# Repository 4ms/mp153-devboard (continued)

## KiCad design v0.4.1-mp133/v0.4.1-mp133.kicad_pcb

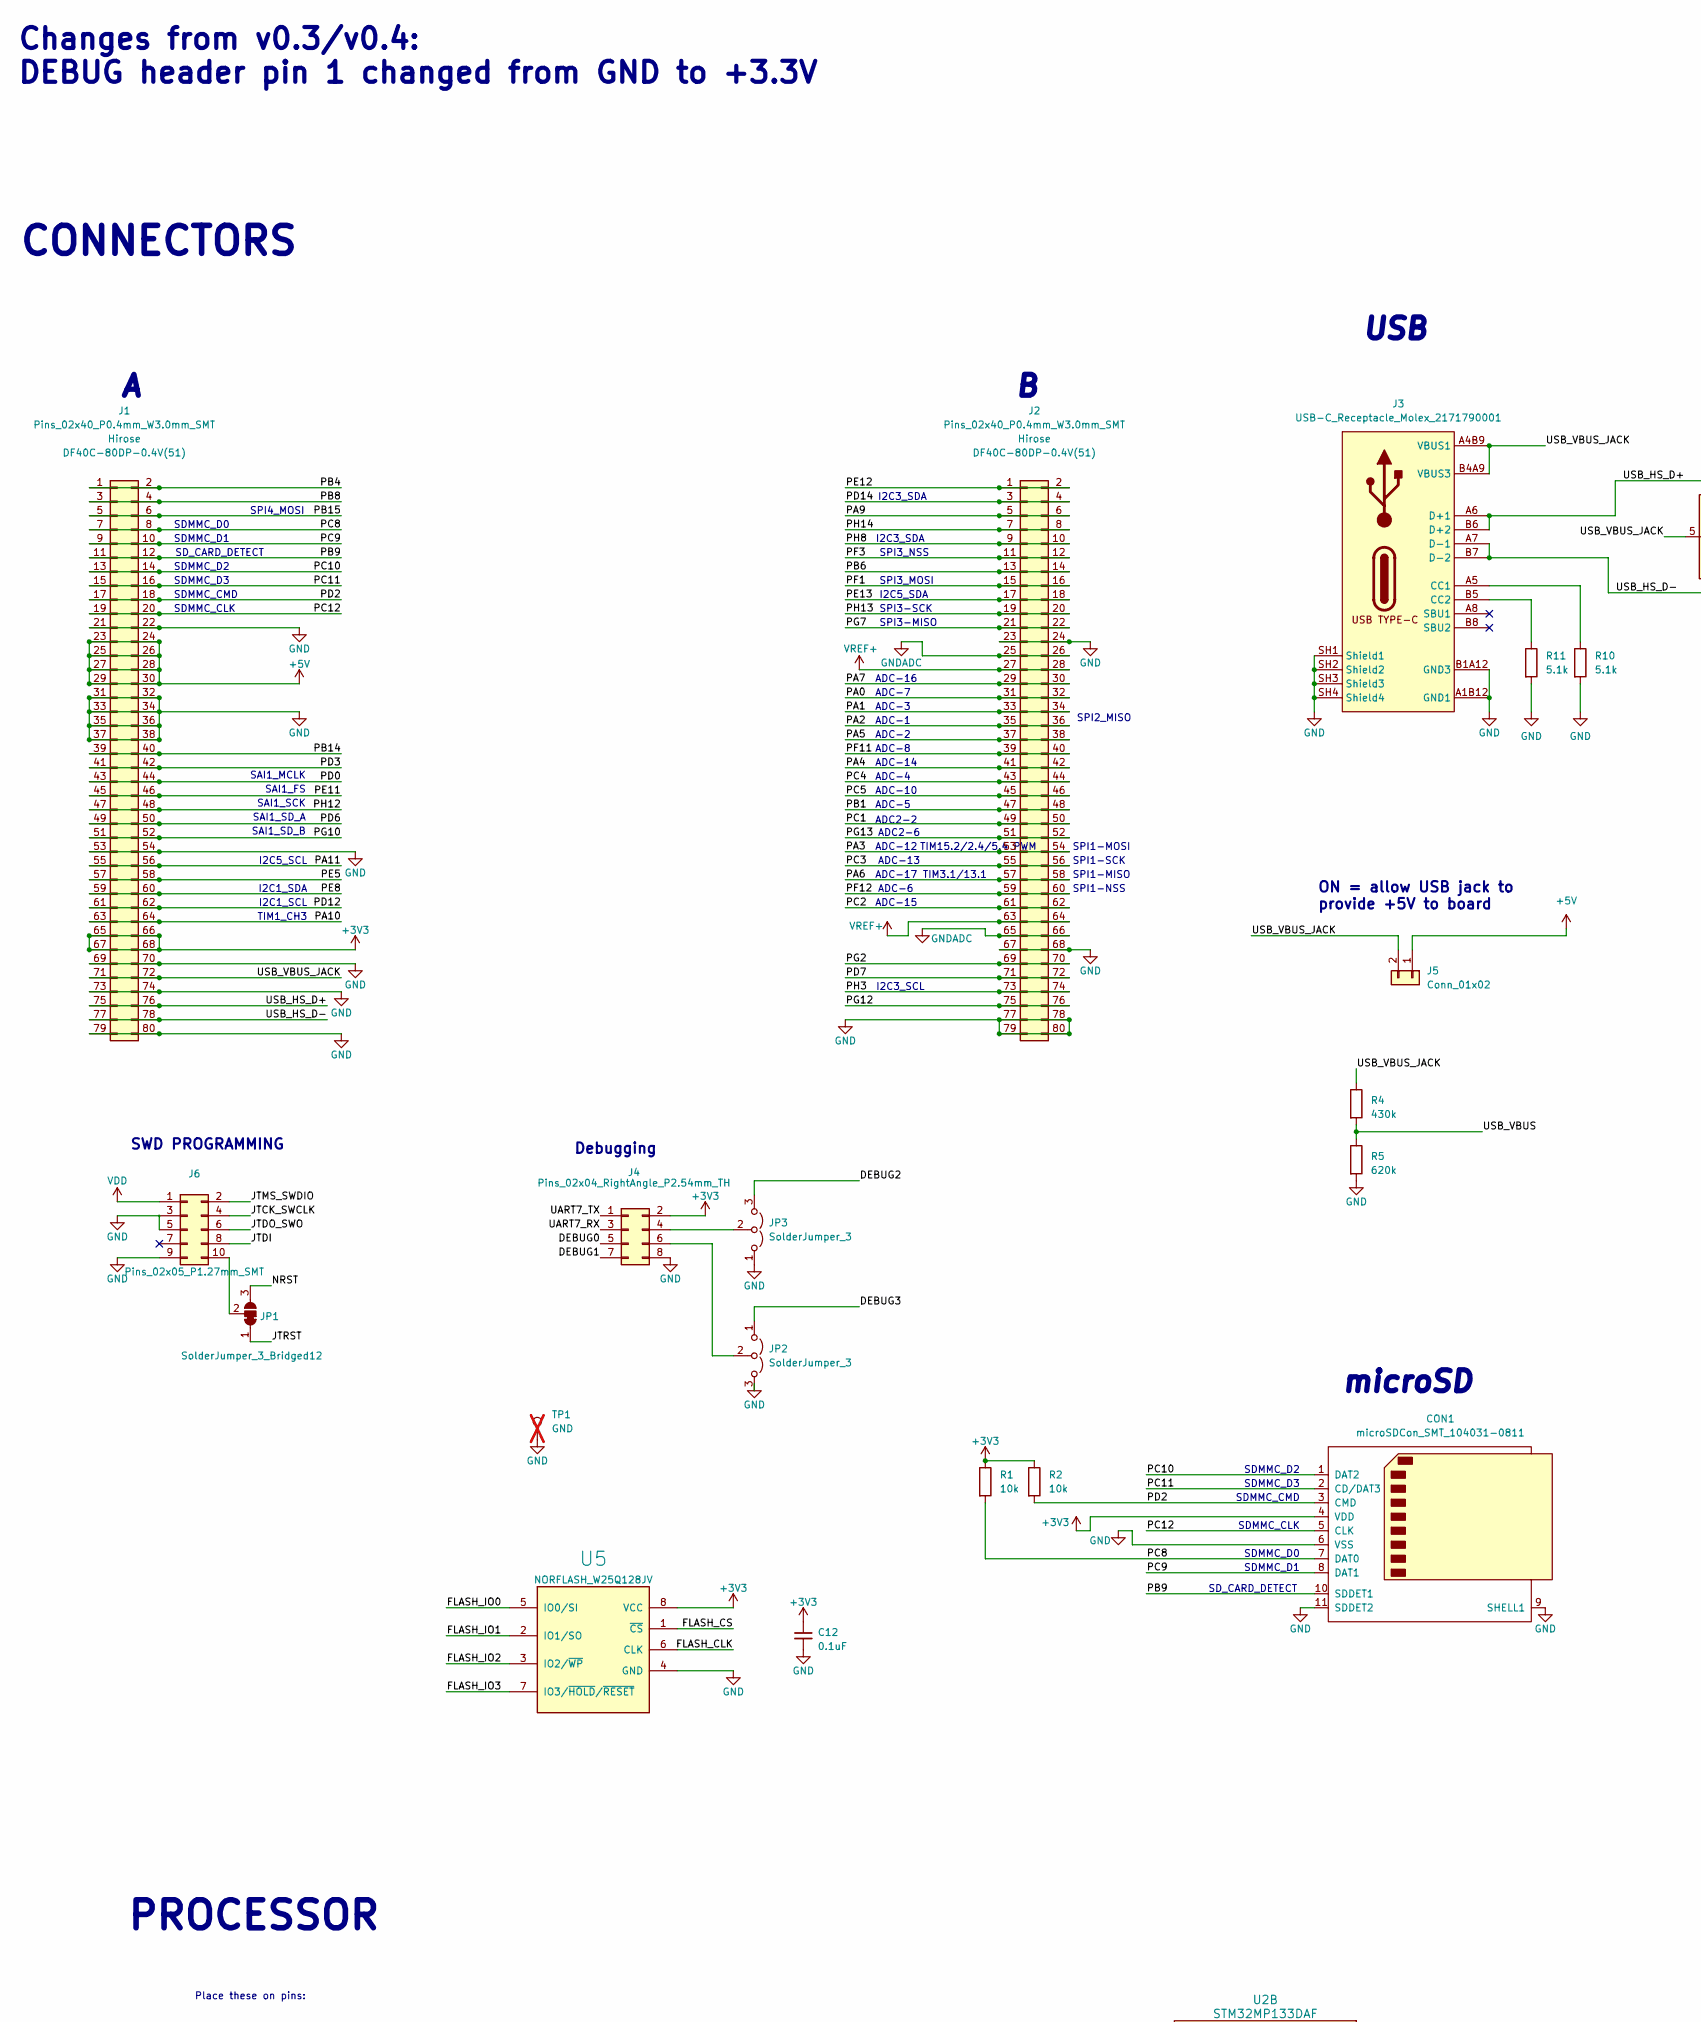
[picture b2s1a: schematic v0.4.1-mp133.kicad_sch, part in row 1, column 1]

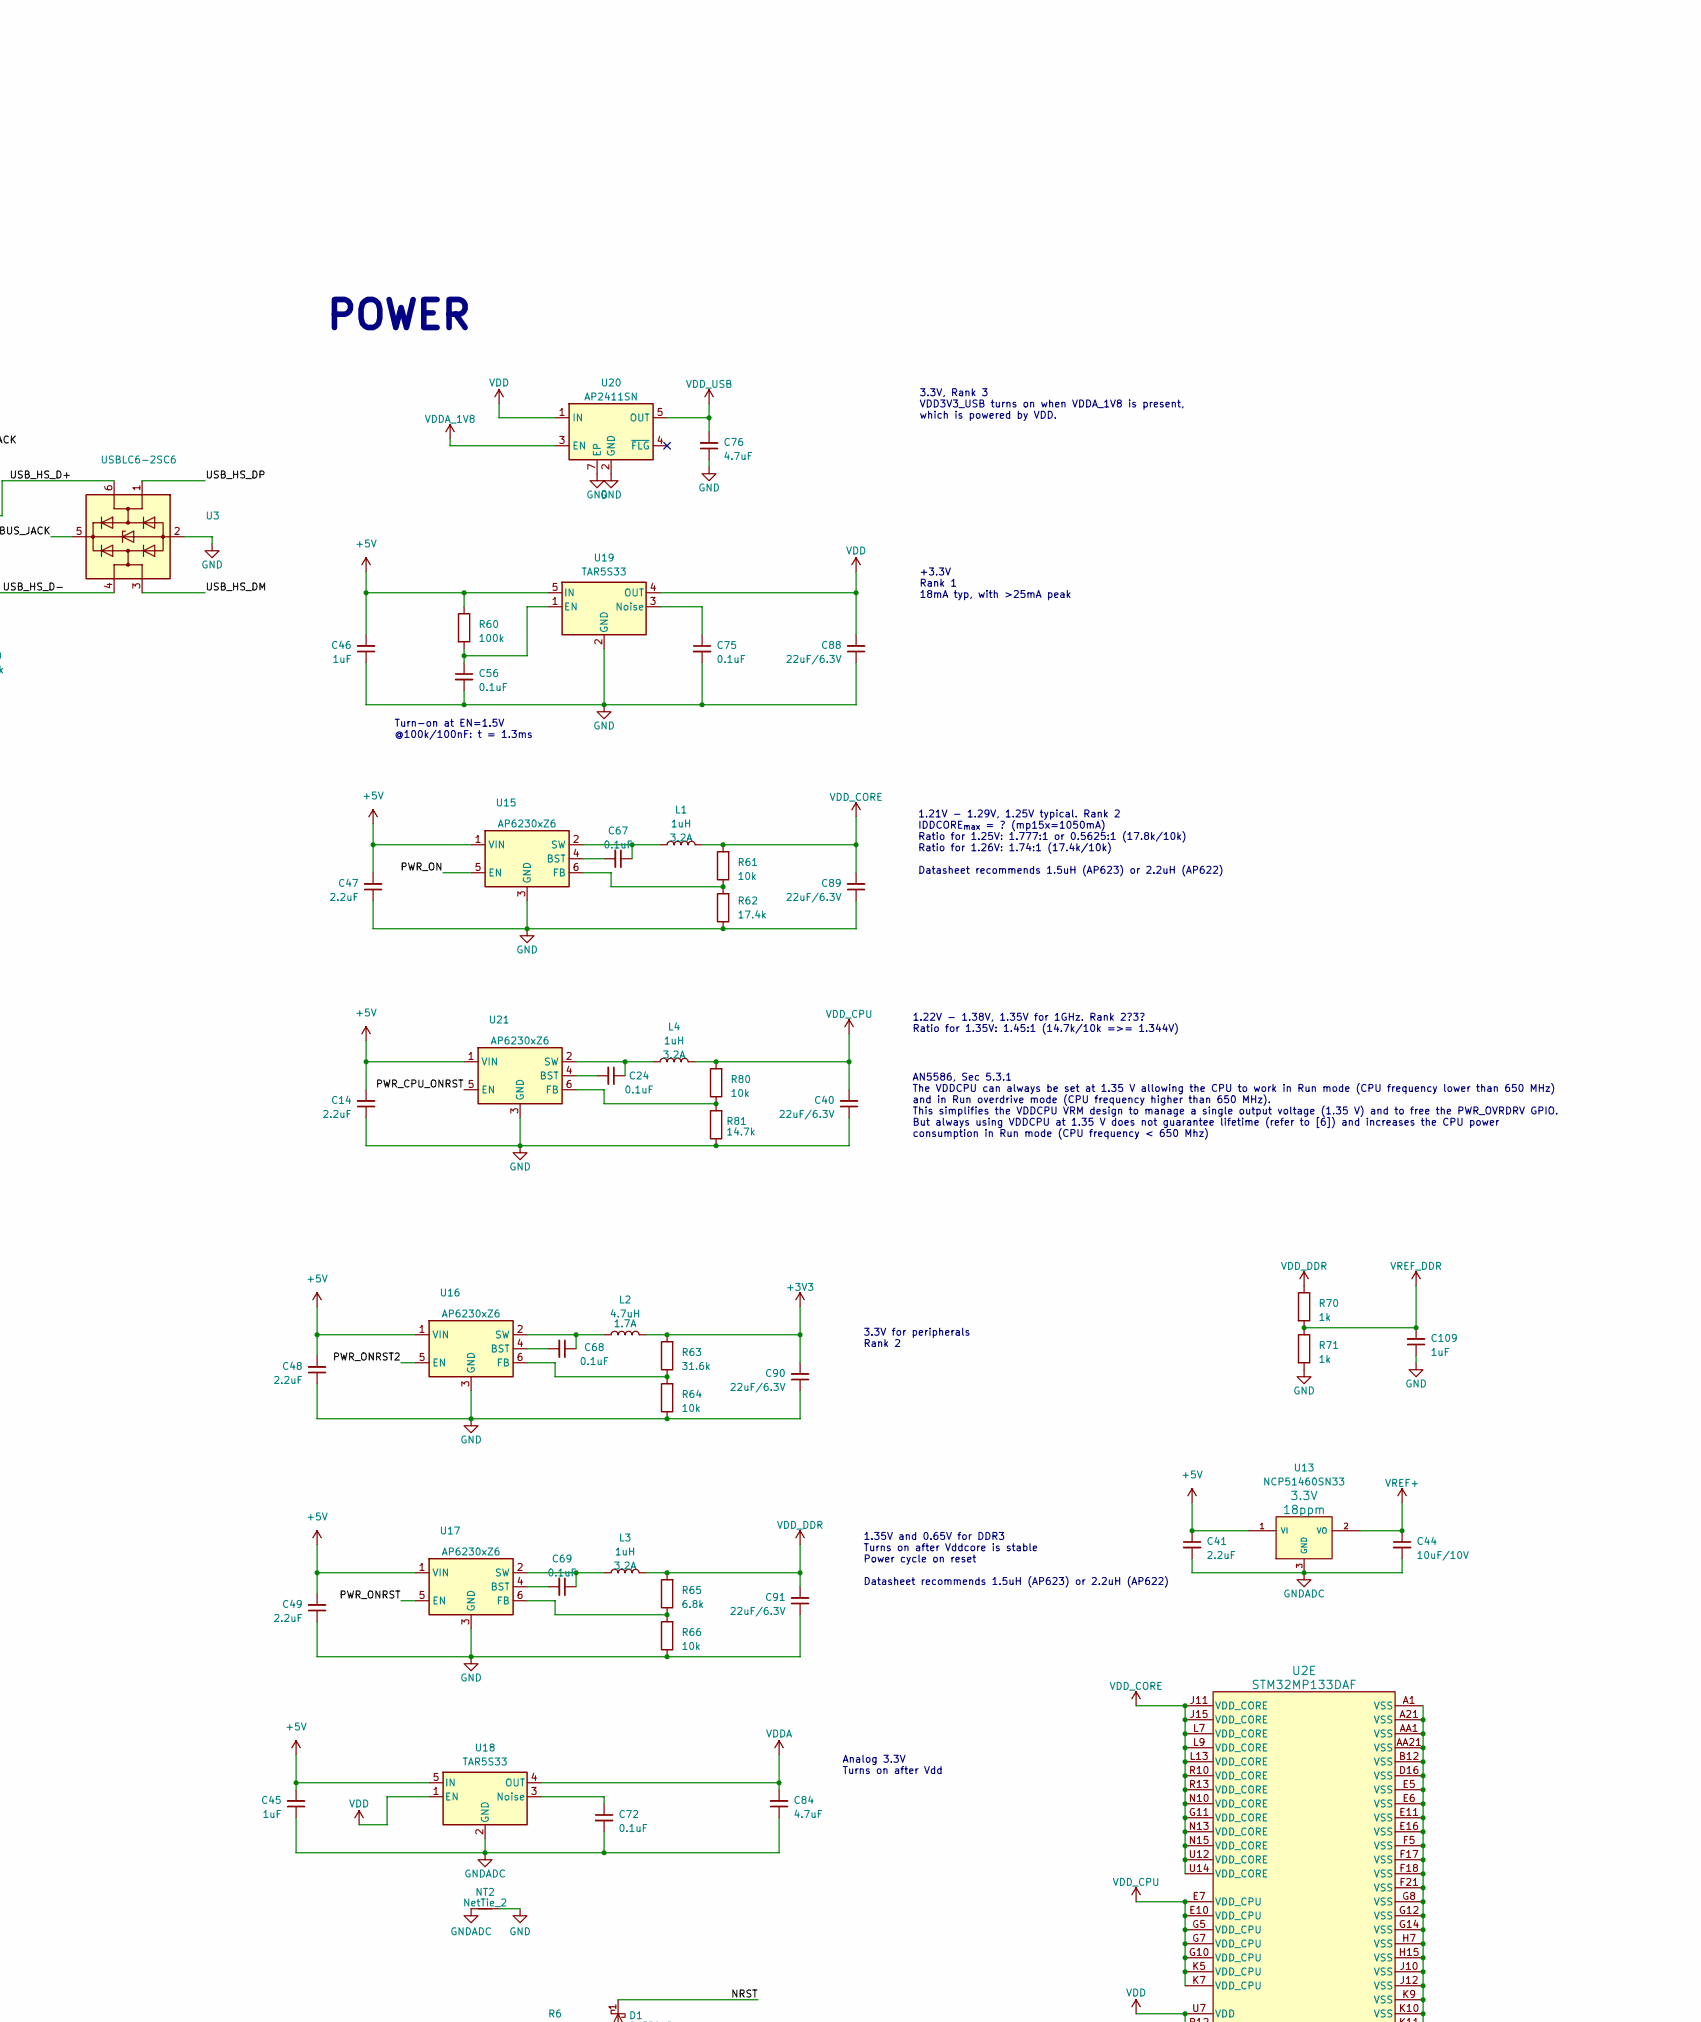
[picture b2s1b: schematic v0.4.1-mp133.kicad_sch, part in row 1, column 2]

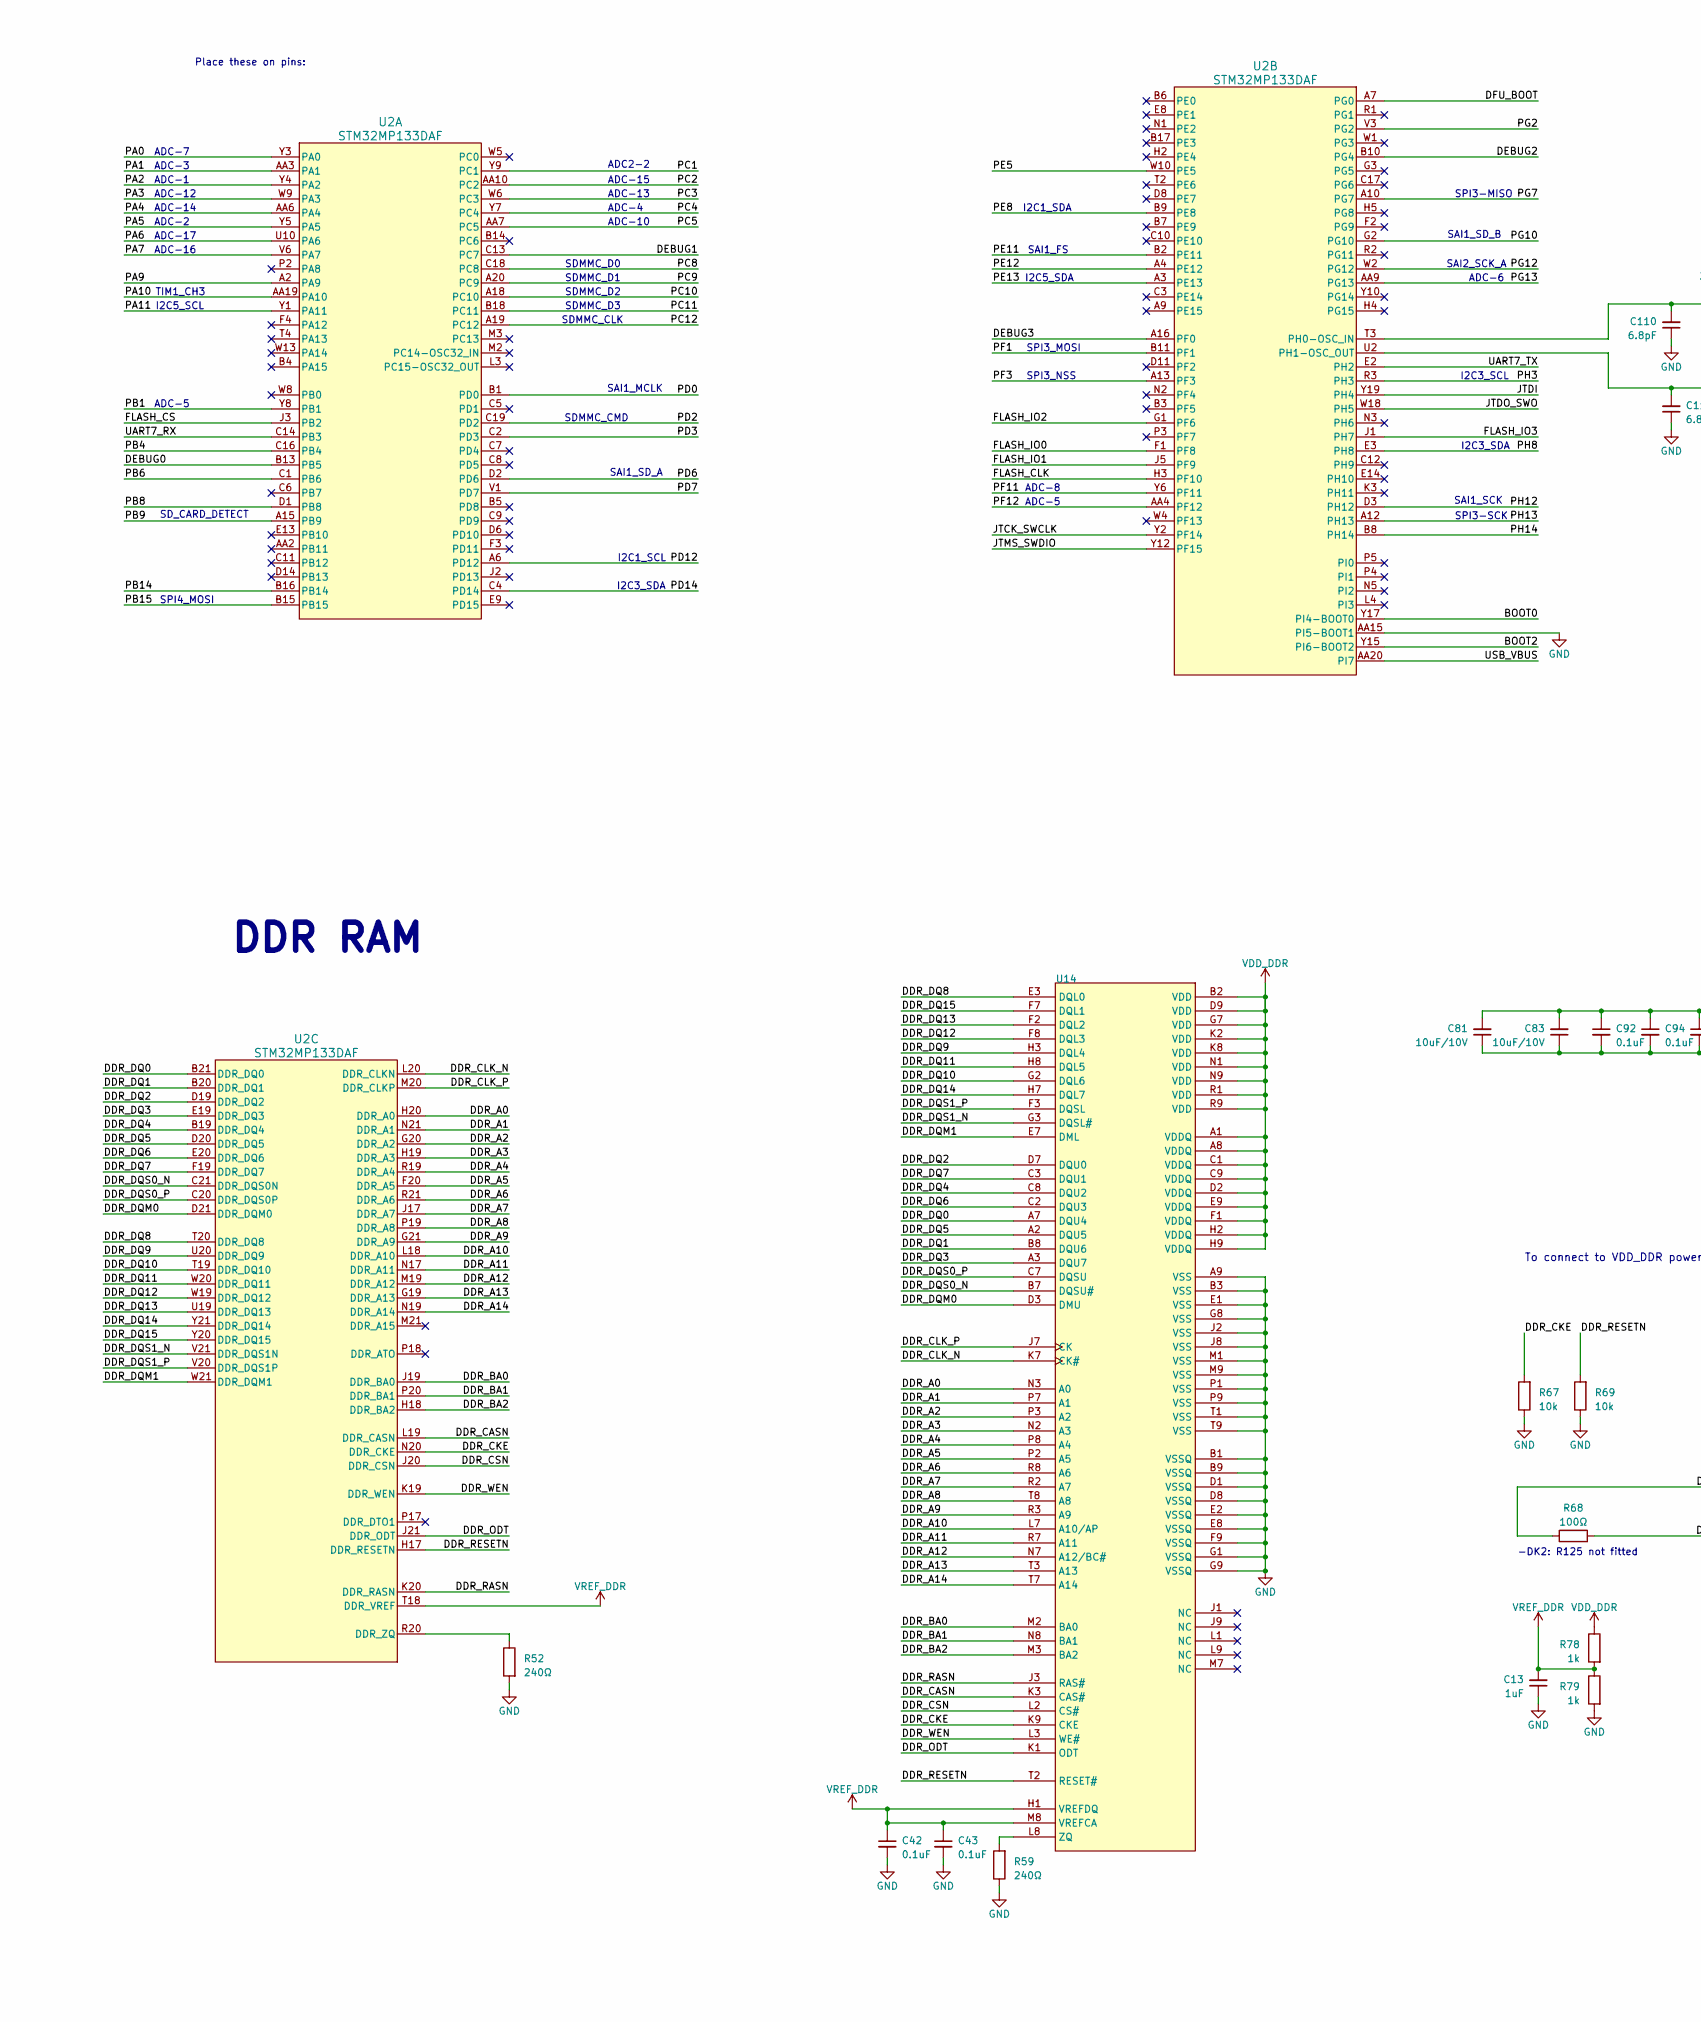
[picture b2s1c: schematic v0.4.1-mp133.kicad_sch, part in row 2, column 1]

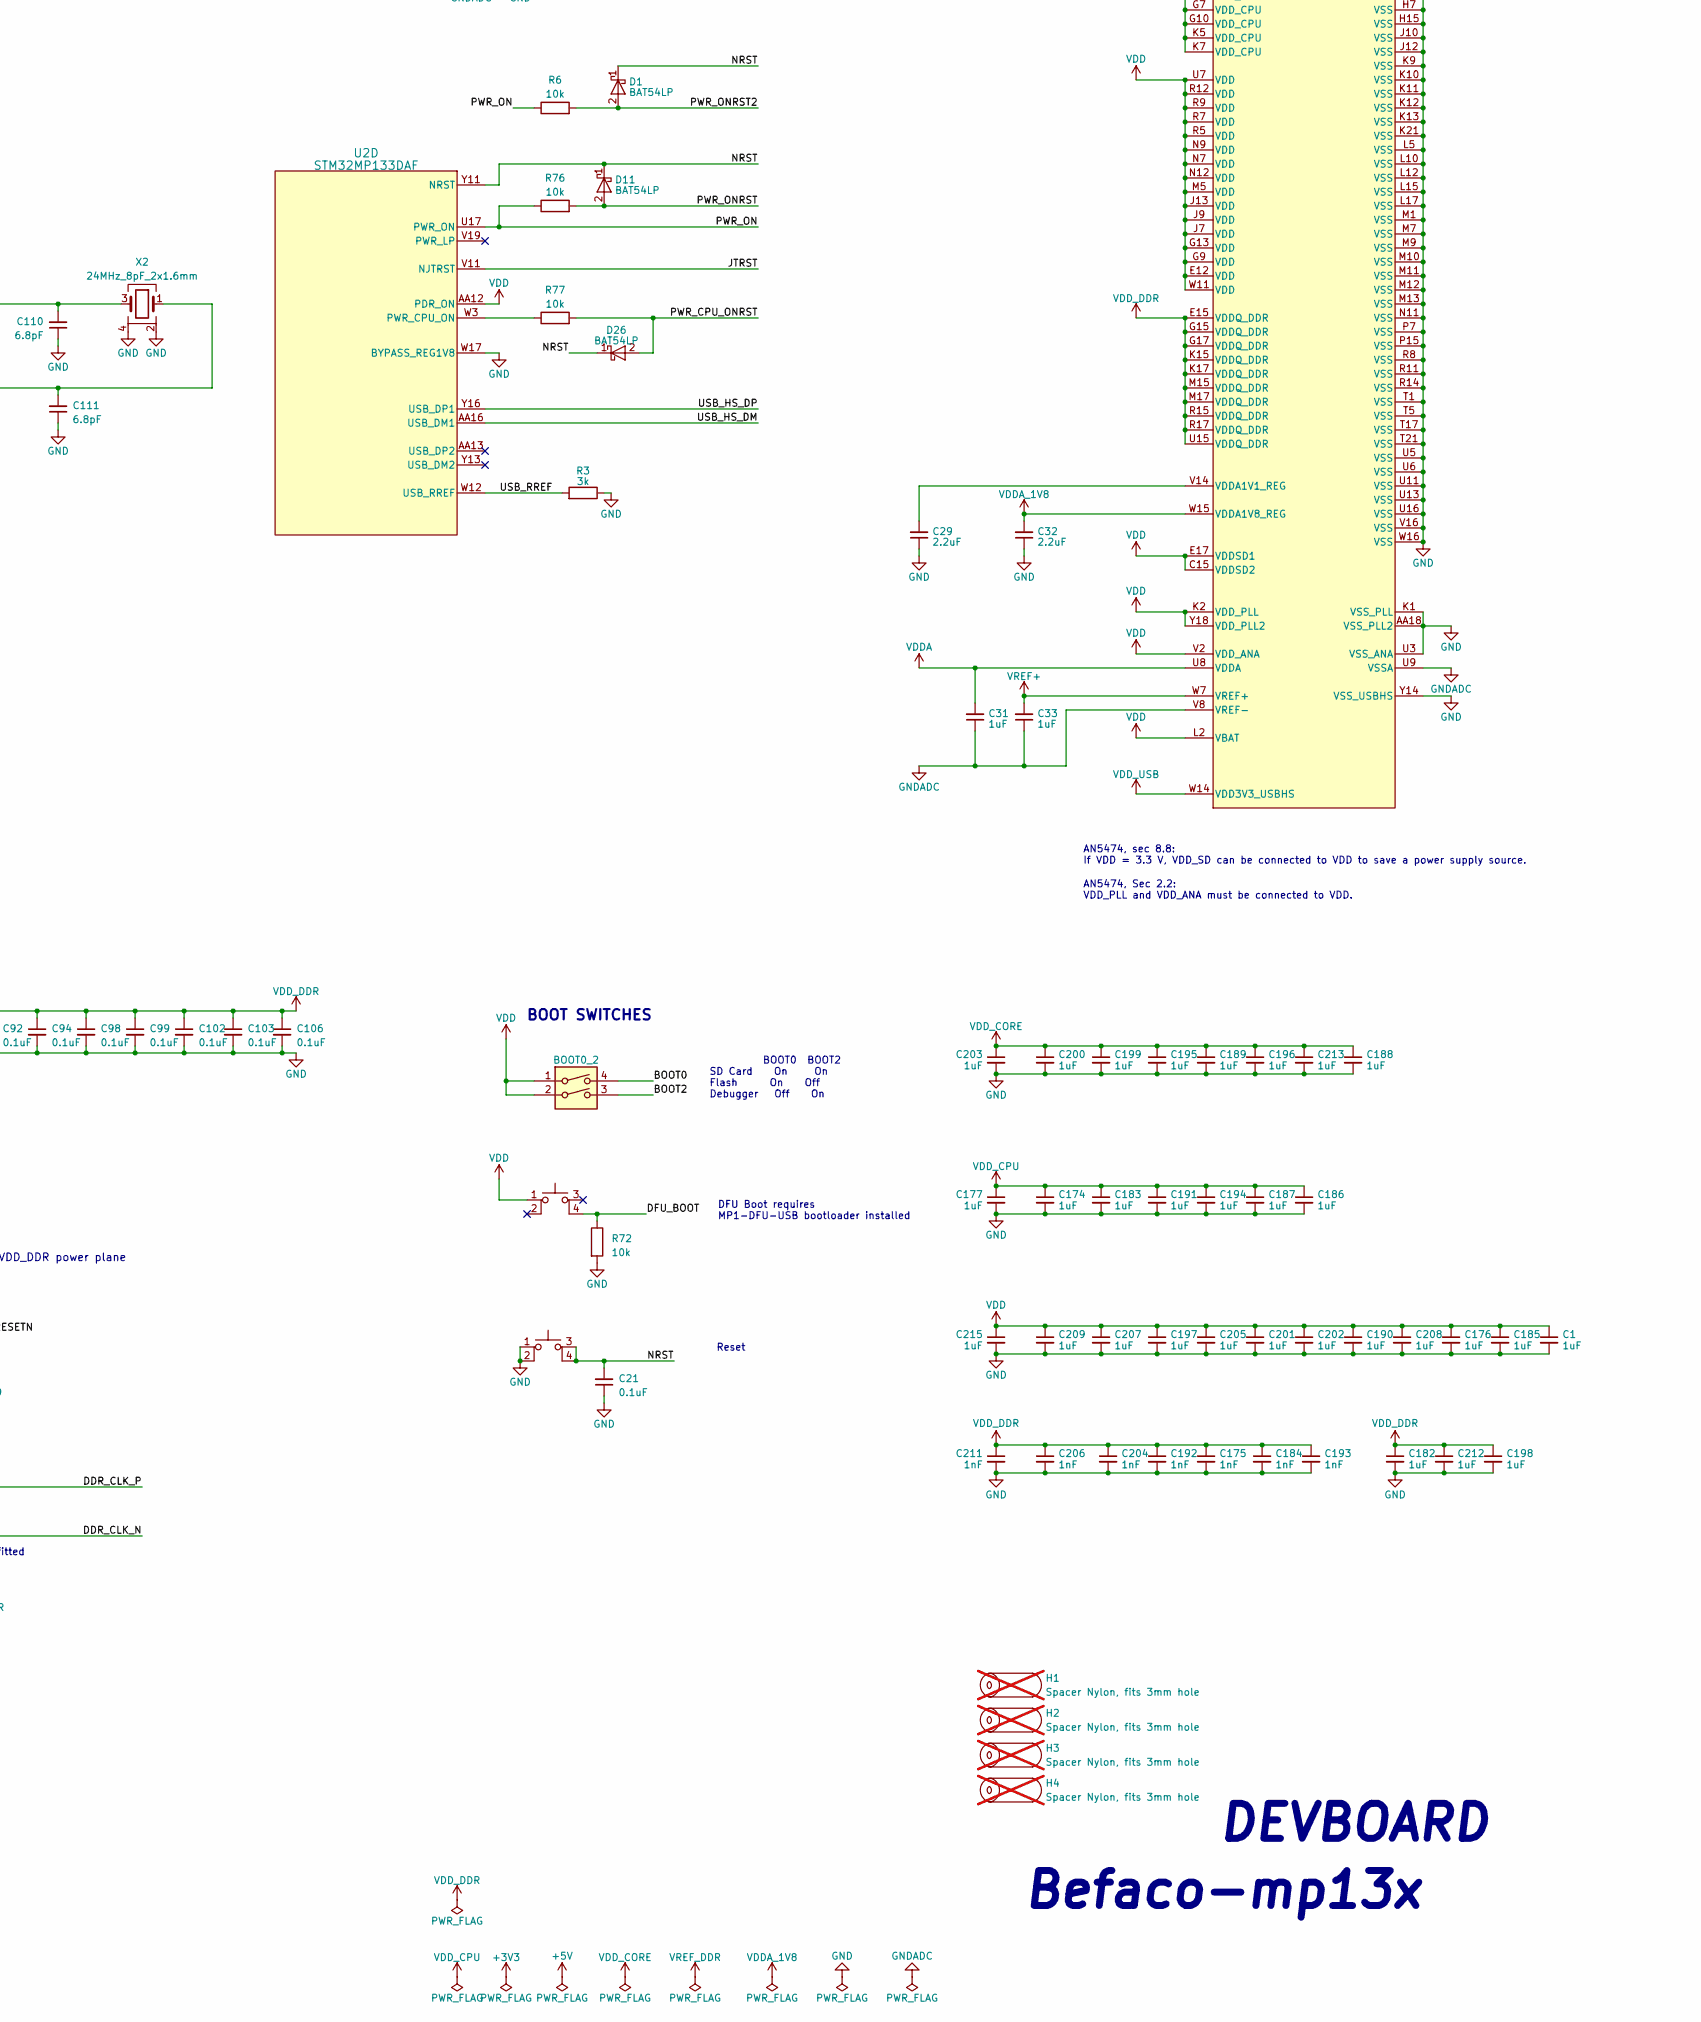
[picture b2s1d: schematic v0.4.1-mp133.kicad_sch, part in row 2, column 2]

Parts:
BOOT0_2: SW_DIP_x02_CTS_219-2MST; SW_DIP_SPSTx02_CTS_219-2MSTR; Part Number 219-2MST; JLCPCB ID C2961978
C1, C174, C176, C177, C182, C183, C185, C186, C187, C188, C189, C190, C191, C194, C195, C196, C197, C198, C199, C200, C201, C202, C203, C205, C207, C208, C209, C212, C213, C215: 1uF_0201_4V; C_0201; Part Number CC0201MRX5R5BB105; JLCPCB ID C272877
C12, C21, C24, C42, C43, C67, C68, C69, C92, C94, C98, C99, C102, C103, C106: 100nF_0402_16V; C_0402; Part Number GCM155R71C104KA55D; JLCPCB ID C1525
C13, C31, C33, C45, C46, C109: 1uF_0402_25V; C_0402; Part Number GMK105CC6105KV-F; JLCPCB ID C52923
C14, C41, C47, C48, C49: 2.2uF_0603_25V; C_0603; Part Number GRM188R6YA225KA12D; JLCPCB ID C57895
C29, C32: 2.2uF_0402_6.3V; C_0402; Part Number GRM155R60J225KE95D; JLCPCB ID C12530
C40, C88, C89, C90, C91: 22uF_0603_6.3V; C_0603; Part Number GRM188R60J226MEA0J; JLCPCB ID C59461
C44, C81, C83: 10uF_0603_10V; C_0603; Part Number GRM188R61A106KE69D; JLCPCB ID C19702
C56, C72, C75: 100nF_0402_50V; C_0402; Part Number GRM155R71H104KE14D; JLCPCB ID C307331
C76, C84: 4.7uF_0402_6.3V; C_0402; Part Number GRM155R60J475ME47; JLCPCB ID C23733
C110, C111: 6.8pF_0402_25V; C_0402; Part Number CC0402CRNPO9BN6R8; JLCPCB ID C1576
C175, C184, C192, C193, C204, C206, C211: 1nF_0201_4V; C_0201; Part Number GRM033R71E102JA01D; JLCPCB ID C258477
CON1: microSDCon_SMT_104031-0811; CardSlot_MicroSD_Molex_104031-0811; Part Number 104031-0811; JLCPCB ID C585350
D1, D11, D26: BAT54LP; DFN-1006-2; Part Number BAT54LP-7; JLCPCB ID C134410
H1, H2, H3, H4: Spacer Nylon, fits 3mm hole; MountingHole_Generic_3mm; not fitted
J1, J2: Pins_02x40_P0.4mm_W3.0mm_SMT; Connector-80pin-P0.4mm-W3.0mm; Part Number DF40C-80DP-0.4V(51); JLCPCB ID C294544
J3: USB-C_Receptacle_Molex_2171790001; USB_C_Receptacle_Molex_2171790001; Part Number 217179-0001; JLCPCB ID C2894899
J4: Pins_02x04_RightAngle_P2.54mm_TH; Pins_2x04_P2.54mm_Horizontal_CroppedSilk; Part Number TSW-104-08-T-D-RA
J5: Conn_01x02; Pins_1x02_2.54mm_TH; Part Number TSW-102-08-T-S-RA
J6: Pins_02x05_P1.27mm_SMT; Pins_2x05_1.27mm_SMD; Part Number FTSH-105-01-F-DV; JLCPCB ID C598540
JP1: SolderJumper_3_Bridged12; JUMPER_SMD_1x3_tiny
JP2, JP3: SolderJumper_3; JUMPER_SMD_1x3_tiny_open
L1, L3, L4: 1uH_3.2A_2520; L_1008_2520Metric; Part Number DFE252012P-1R0M=P2; JLCPCB ID C435392
L2: 4.7uH_1.7A_2510; L_Wuerth_MAPI-2510; Part Number SRN2510F-4R7M; JLCPCB ID C2047781
NT2: NetTie_2; NetTie-2_SMD_Pad0.16mm_6mil
R1, R2, R6, R61, R64, R66, R67, R69, R72, R76, R77, R80: 10k_0402; R_0402; Part Number RC0402FR-0710KL; JLCPCB ID C60490
R3: 3k_0402; R_0402; Part Number RC0402FR-073KL; JLCPCB ID C137987
R4: 430k_0402; R_0402; Part Number RC0402FR-07430KL; JLCPCB ID C163463
R5: 620k_0402; R_0402; Part Number RC0402FR-07620KL; JLCPCB ID C137952
R10, R11: 5.1k_0402; R_0402; Part Number RC0402FR-075K1L; JLCPCB ID C105872
R52, R59: 240Ω_0402; R_0402; Part Number RC0402FR-07240RL; JLCPCB ID C114755
R60: 100k_0402; R_0402; Part Number RC0402FR-07100KL; JLCPCB ID C60491
R62: 17.4k_0402; R_0402; Part Number RC0402FR-0717K4L; JLCPCB ID C327366
R63: 31.6k_0402; R_0402; Part Number RC0402FR-0731K6L; JLCPCB ID C276265
R65: 6.8k_0402; R_0402; Part Number RC0402FR-076K8L; JLCPCB ID C93940
R68: 100Ω_0402; R_0402; Part Number RC0402FR-07100RL; JLCPCB ID C106232
R70, R71, R78, R79: 1k_0402; R_0402; Part Number RC0402FR-071KL; JLCPCB ID C106235
R81: 14.7k_0402; R_0402; Part Number RC0402FR-0714K7L; JLCPCB ID C138055
S2, S3: SW_Push_PTS526 SM15 SMTR2 LFS; Button_Tact_PTS526; Part Number PTS526 SM15 SMTR2 LFS; JLCPCB ID C2689521
TP1: GND; PinHeader_1x01_P2.54mm_Vertical; not fitted
U2: STM32MP133DAF; TFBGA-320_11x11mm_P0.5; Part Number STM32MP133DAF
U3: USBLC6-2SC6; SOT-23-6; Part Number USBLC6-2SC6; JLCPCB ID C2827654
U5: NORFLASH_W25Q128JV; SOIC-8_5.28x4.9mm_Pitch1.27mm; Part Number W25Q128JVSIQ; JLCPCB ID C113767
U13: NCP51460SN33; SOT23-3_PO132; Part Number NCP51460SN33T1G; JLCPCB ID C233715
U14: DDR3L-RAM-4Gb_MT41K256M16TW; FBGA-96_Layout2x3x16_Body8x14_P0.8mm; Part Number MT41K256M16TW-107-P-V00H; JLCPCB ID C253882
U15, U16, U17, U21: AP6230xZ6; SOT-563; Part Number AP62301Z6-7; JLCPCB ID C1880992
U18, U19: TAR5S33; SOT-23-5; Part Number TAR5S33TE85LF; JLCPCB ID C2762700
U20: AP2411SN; DFN-6-1EP_2x2mm_P0.65mm_EP1x1.6mm; Part Number AP2411SN-7; JLCPCB ID C2149815
X2: 24MHz_8pF_2x1.6mm; Crystal_2.0x1.6mm_4pin; Part Number ECS-240-8-37-CKM-TR3; JLCPCB ID C1986107

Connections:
+3V3: C12.1, C90.2, CON1.4 (VDD), J1.65, J1.66, J1.67, J1.68, J4.2, L2.2, R1.1, R2.1, R63.2, U5.8 (VCC)
+5V: C14.2, C41.1, C45.2, C46.2, C47.2, C48.2, C49.2, J1.23, J1.24, J1.25, J1.26, J1.27, J1.28, J1.29, J1.30, J5.1, R60.1, U13.1 (VI), U15.1 (VIN), U16.1 (VIN), U17.1 (VIN), U18.5 (IN), U19.5 (IN), U21.1 (VIN)
/BOOT0: BOOT0_2.4, U2.Y17 (PI4-BOOT0)
/BOOT2: BOOT0_2.3, U2.Y15 (PI6-BOOT2)
/DDR_A0: U2.H20 (DDR_A0), U14.N3 (A0)
/DDR_A1: U2.N21 (DDR_A1), U14.P7 (A1)
/DDR_A2: U2.G20 (DDR_A2), U14.P3 (A2)
/DDR_A3: U2.H19 (DDR_A3), U14.N2 (A3)
/DDR_A4: U2.R19 (DDR_A4), U14.P8 (A4)
/DDR_A5: U2.F20 (DDR_A5), U14.P2 (A5)
/DDR_A6: U2.R21 (DDR_A6), U14.R8 (A6)
/DDR_A7: U2.J17 (DDR_A7), U14.R2 (A7)
/DDR_A8: U2.P19 (DDR_A8), U14.T8 (A8)
/DDR_A9: U2.G21 (DDR_A9), U14.R3 (A9)
/DDR_A10: U2.L18 (DDR_A10), U14.L7 (A10/AP)
/DDR_A11: U2.N17 (DDR_A11), U14.R7 (A11)
/DDR_A12: U2.M19 (DDR_A12), U14.N7 (A12/BC#)
/DDR_A13: U2.G19 (DDR_A13), U14.T3 (A13)
/DDR_A14: U2.N19 (DDR_A14), U14.T7 (A14)
/DDR_BA0: U2.J19 (DDR_BA0), U14.M2 (BA0)
/DDR_BA1: U2.P20 (DDR_BA1), U14.N8 (BA1)
/DDR_BA2: U2.H18 (DDR_BA2), U14.M3 (BA2)
/DDR_CASN: U2.L19 (DDR_CASN), U14.K3 (CAS#)
/DDR_CKE: R67.2, U2.N20 (DDR_CKE), U14.K9 (CKE)
/DDR_CLK_N: R68.2, U2.L20 (DDR_CLKN), U14.K7 (CK#)
/DDR_CLK_P: R68.1, U2.M20 (DDR_CLKP), U14.J7 (CK)
/DDR_CSN: U2.J20 (DDR_CSN), U14.L2 (CS#)
/DDR_DQ0: U2.B21 (DDR_DQ0), U14.A7 (DQU4)
/DDR_DQ1: U2.B20 (DDR_DQ1), U14.B8 (DQU6)
/DDR_DQ2: U2.D19 (DDR_DQ2), U14.D7 (DQU0)
/DDR_DQ3: U2.E19 (DDR_DQ3), U14.A3 (DQU7)
/DDR_DQ4: U2.B19 (DDR_DQ4), U14.C8 (DQU2)
/DDR_DQ5: U2.D20 (DDR_DQ5), U14.A2 (DQU5)
/DDR_DQ6: U2.E20 (DDR_DQ6), U14.C2 (DQU3)
/DDR_DQ7: U2.F19 (DDR_DQ7), U14.C3 (DQU1)
/DDR_DQ8: U2.T20 (DDR_DQ8), U14.E3 (DQL0)
/DDR_DQ9: U2.U20 (DDR_DQ9), U14.H3 (DQL4)
/DDR_DQ10: U2.T19 (DDR_DQ10), U14.G2 (DQL6)
/DDR_DQ11: U2.W20 (DDR_DQ11), U14.H8 (DQL5)
/DDR_DQ12: U2.W19 (DDR_DQ12), U14.F8 (DQL3)
/DDR_DQ13: U2.U19 (DDR_DQ13), U14.F2 (DQL2)
/DDR_DQ14: U2.Y21 (DDR_DQ14), U14.H7 (DQL7)
/DDR_DQ15: U2.Y20 (DDR_DQ15), U14.F7 (DQL1)
/DDR_DQM0: U2.D21 (DDR_DQM0), U14.D3 (DMU)
/DDR_DQM1: U2.W21 (DDR_DQM1), U14.E7 (DML)
/DDR_DQS0_N: U2.C21 (DDR_DQS0N), U14.B7 (DQSU#)
/DDR_DQS0_P: U2.C20 (DDR_DQS0P), U14.C7 (DQSU)
/DDR_DQS1_N: U2.V21 (DDR_DQS1N), U14.G3 (DQSL#)
/DDR_DQS1_P: U2.V20 (DDR_DQS1P), U14.F3 (DQSL)
/DDR_ODT: U2.J21 (DDR_ODT), U14.K1 (ODT)
/DDR_RASN: U2.K20 (DDR_RASN), U14.J3 (RAS#)
/DDR_RESETN: R69.2, U2.H17 (DDR_RESETN), U14.T2 (RESET#)
/DDR_WEN: U2.K19 (DDR_WEN), U14.L3 (WE#)
/DEBUG0: J4.5, U2.B13 (PB5)
/DEBUG1: J4.7, U2.C13 (PC7)
/DEBUG2: JP3.3 (B), U2.B10 (PG4)
/DEBUG3: JP2.1 (A), U2.A16 (PF0)
/DFU_BOOT: R72.1, S3.4, U2.A7 (PG0)
/FLASH_CLK: U2.H3 (PF10), U5.6 (CLK)
/FLASH_CS: U2.J3 (PB2), U5.1 (~CS)
/FLASH_IO0: U2.F1 (PF8), U5.5 (IO0/SI)
/FLASH_IO1: U2.J5 (PF9), U5.2 (IO1/SO)
/FLASH_IO2: U2.G1 (PF6), U5.3 (IO2/~WP)
/FLASH_IO3: U2.J1 (PH7), U5.7 (IO3/~HOLD/~RESET)
/JTCK_SWCLK: J6.4, U2.Y2 (PF14)
/JTDI: J6.8, U2.Y19 (PH4)
/JTDO_SWO: J6.6, U2.W18 (PH5)
/JTMS_SWDIO: J6.2, U2.Y12 (PF15)
/JTRST: JP1.1 (A), U2.V11 (NJTRST)
/NRST: C21.2, D1.1 (K), D11.1 (K), D26.1 (K), JP1.3 (B), S2.3, S2.4, U2.Y11 (NRST)
/PA0: J2.31, J2.32, U2.Y3 (PA0)
/PA1: J2.33, J2.34, U2.AA3 (PA1)
/PA2: J2.35, J2.36, U2.Y4 (PA2)
/PA3: J2.53, J2.54, U2.W9 (PA3)
/PA4: J2.41, J2.42, U2.AA6 (PA4)
/PA5: J2.37, J2.38, U2.Y5 (PA5)
/PA6: J2.57, J2.58, U2.U10 (PA6)
/PA7: J2.29, J2.30, U2.V6 (PA7)
/PA9: J2.5, J2.6, U2.A2 (PA9)
/PA10: J1.63, J1.64, U2.AA19 (PA10)
/PA11: J1.55, J1.56, U2.Y1 (PA11)
/PB1: J2.47, J2.48, U2.Y8 (PB1)
/PB4: J1.1, J1.2, U2.C16 (PB4)
/PB6: J2.13, J2.14, U2.C1 (PB6)
/PB8: J1.3, J1.4, U2.D1 (PB8)
/PB9: CON1.10 (SDDET1), J1.11, J1.12, U2.A15 (PB9)
/PB14: J1.39, J1.40, U2.B16 (PB14)
/PB15: J1.5, J1.6, U2.B15
/PC1: J2.49, J2.50, U2.Y9 (PC1)
/PC2: J2.61, J2.62, U2.AA10 (PC2)
/PC3: J2.55, J2.56, U2.W6 (PC3)
/PC4: J2.43, J2.44, U2.Y7 (PC4)
/PC5: J2.45, J2.46, U2.AA7 (PC5)
/PC8: CON1.7 (DAT0), J1.7, J1.8, R1.2, U2.C18 (PC8)
/PC9: CON1.8 (DAT1), J1.9, J1.10, U2.A20 (PC9)
/PC10: CON1.1 (DAT2), J1.13, J1.14, U2.A18 (PC10)
/PC11: CON1.2 (CD/DAT3), J1.15, J1.16, U2.B18 (PC11)
/PC12: CON1.5 (CLK), J1.19, J1.20, U2.A19 (PC12)
/PD0: J1.43, J1.44, U2.B1 (PD0)
/PD2: CON1.3 (CMD), J1.17, J1.18, R2.2, U2.C19 (PD2)
/PD3: J1.41, J1.42, U2.C2 (PD3)
/PD6: J1.49, J1.50, U2.D2 (PD6)
/PD7: J2.71, J2.72, U2.V1 (PD7)
/PD12: J1.61, J1.62, U2.A6 (PD12)
/PD14: J2.3, J2.4, U2.C4 (PD14)
/PE5: J1.57, J1.58, U2.W10 (PE5)
/PE8: J1.59, J1.60, U2.B9 (PE8)
/PE11: J1.45, J1.46, U2.B2 (PE11)
/PE12: J2.1, J2.2, U2.A4 (PE12)
/PE13: J2.17, J2.18, U2.A3 (PE13)
/PF1: J2.15, J2.16, U2.B11 (PF1)
/PF3: J2.11, J2.12, U2.A13 (PF3)
/PF11: J2.39, J2.40, U2.Y6 (PF11)
/PF12: J2.59, J2.60, U2.AA4 (PF12)
/PG2: J2.69, J2.70, U2.V3 (PG2)
/PG7: J2.21, J2.22, U2.A10 (PG7)
/PG10: J1.51, J1.52, U2.G2 (PG10)
/PG12: J2.75, J2.76, U2.W2 (PG12)
/PG13: J2.51, J2.52, U2.AA9 (PG13)
/PH3: J2.73, J2.74, U2.R3 (PH3)
/PH8: J2.9, J2.10, U2.E3 (PH8)
/PH12: J1.47, J1.48, U2.D3 (PH12)
/PH13: J2.19, J2.20, U2.A12 (PH13)
/PH14: J2.7, J2.8, U2.B8 (PH14)
/PWR_CPU_ONRST: D26.2 (A), R77.2, U21.5 (EN)
/PWR_ON: R6.1, R76.1, U2.U17 (PWR_ON), U15.5 (EN)
/PWR_ONRST: D11.2 (A), R76.2, U17.5 (EN)
/PWR_ONRST2: D1.2 (A), R6.2, U16.5 (EN)
/UART7_RX: J4.3, U2.C14 (PB3)
/UART7_TX: J4.1, U2.E2 (PH2)
/USB_HS_D+: J1.75, J1.76, J3.A6 (D+1), J3.B6 (D+2), U3.6 (I/O1)
/USB_HS_D-: J1.77, J1.78, J3.A7 (D-1), J3.B7 (D-2), U3.4 (I/O2)
/USB_HS_DM: U2.AA16 (USB_DM1), U3.3 (I/O2)
/USB_HS_DP: U2.Y16 (USB_DP1), U3.1 (I/O1)
/USB_RREF: R3.2, U2.W12 (USB_RREF)
/USB_VBUS: R4.2, R5.1, U2.AA20 (PI7)
/USB_VBUS_JACK: J1.71, J1.72, J3.A4B9 (VBUS1), J3.B4A9 (VBUS3), J5.2, R4.1, U3.5 (VBUS)
GND: C1.2, C12.2, C13.1, C14.1, C21.1, C29.1, C32.1, C40.1, C42.2, C43.2, C46.1, C47.1, C48.1, C49.1, C56.2, C75.2, C76.1, C81.1, C83.1, C88.1, C89.1, C90.1, C91.1, C92.2, C94.2, C98.2, C99.2, C102.2, C103.2, C106.2, C109.1, C110.1, C111.1, C174.2, C175.2, C176.2, C177.2, C182.2, C183.2, C184.2, C185.2, C186.2, C187.2, C188.2, C189.2, C190.2, C191.2, C192.2, C193.2, C194.2, C195.2, C196.2, C197.2, C198.2, C199.2, C200.2, C201.2, C202.2, C203.2, C204.2, C205.2, C206.2, C207.2, C208.2, C209.2, C211.2, C212.2, C213.2, C215.2, CON1.6 (VSS), CON1.9 (SHELL1), CON1.11 (SDDET2), J1.21, J1.22, J1.31, J1.32, J1.33, J1.34, J1.35, J1.36, J1.37, J1.38, J1.53, J1.54, J1.69, J1.70, J1.73, J1.74, J1.79, J1.80, J2.23, J2.24, J2.67, J2.68, J2.77, J2.78, J2.79, J2.80, J3.A1B12 (GND1), J3.B1A12 (GND3), J3.SH1 (Shield1), J3.SH2 (Shield2), J3.SH3 (Shield3), J3.SH4 (Shield4), J4.8, J6.3, J6.5, J6.9, JP2.3 (B), JP3.1 (A), NT2.2, R3.1, R5.2, R10.2, R11.2, R52.2, R59.1, R62.1, R64.1, R66.1, R67.1, R69.1, R71.2, R72.2, R79.2, R81.1, S2.1, S2.2, TP1.1, U2.A1 (VSS), U2.A21 (VSS), U2.AA1 (VSS), U2.AA15 (PI5-BOOT1), U2.AA18 (VSS_PLL2), U2.AA21 (VSS), U2.B12 (VSS), U2.D16 (VSS), U2.E5 (VSS), U2.E6 (VSS), U2.E11 (VSS), U2.E16 (VSS), U2.F5 (VSS), U2.F17 (VSS), U2.F18 (VSS), U2.F21 (VSS), U2.G8 (VSS), U2.G12 (VSS), U2.G14 (VSS), U2.H7 (VSS), U2.H15 (VSS), U2.J10 (VSS), U2.J12 (VSS), U2.K1 (VSS_PLL), U2.K9 (VSS), U2.K10 (VSS), U2.K11 (VSS), U2.K12 (VSS), U2.K13 (VSS), U2.K21 (VSS), U2.L5 (VSS), U2.L10 (VSS), U2.L12 (VSS), U2.L15 (VSS), U2.L17 (VSS), U2.M1 (VSS), U2.M7 (VSS), U2.M9 (VSS), U2.M10 (VSS), U2.M11 (VSS), U2.M12 (VSS), U2.M13 (VSS), U2.N11 (VSS), U2.P7 (VSS), U2.P15 (VSS), U2.R8 (VSS), U2.R11 (VSS), U2.R14 (VSS), U2.T1 (VSS), U2.T5 (VSS), U2.T17 (VSS), U2.T21 (VSS), U2.U3 (VSS_ANA), U2.U5 (VSS), U2.U6 (VSS), U2.U11 (VSS), U2.U13 (VSS), U2.U16 (VSS), U2.V16 (VSS), U2.W16 (VSS), U2.W17 (BYPASS_REG1V8), U2.Y14 (VSS_USBHS), U3.2 (GND), U5.4 (GND), U14.A9 (VSS), U14.B1 (VSSQ), U14.B3 (VSS), U14.B9 (VSSQ), U14.D1 (VSSQ), U14.D8 (VSSQ), U14.E1 (VSS), U14.E2 (VSSQ), U14.E8 (VSSQ), U14.F9 (VSSQ), U14.G1 (VSSQ), U14.G8 (VSS), U14.G9 (VSSQ), U14.J2 (VSS), U14.J8 (VSS), U14.M1 (VSS), U14.M9 (VSS), U14.P1 (VSS), U14.P9 (VSS), U14.T1 (VSS), U14.T9 (VSS), U15.3 (GND), U16.3 (GND), U17.3 (GND), U19.2 (GND), U20.2 (GND), U20.7 (EP), U21.3 (GND), X2.2, X2.4
GNDADC: C31.1, C33.1, C41.2, C44.2, C45.1, C72.2, C84.1, J2.25, J2.26, J2.65, J2.66, NT2.1, U2.U9 (VSSA), U2.V8 (VREF-), U13.3 (GND), U18.2 (GND)
unnamed: J3.A5 (CC1), R10.1
unnamed: J3.B5 (CC2), R11.1
unnamed: J4.4, JP3.2 (C)
unnamed: J4.6, JP2.2 (C)
unnamed: J6.10, JP1.2 (C)
unnamed: C110.2, U2.T3 (PH0-OSC_IN), X2.3
unnamed: C111.2, U2.U2 (PH1-OSC_OUT), X2.1
unnamed: R52.1, U2.R20 (DDR_ZQ)
unnamed: R77.1, U2.W3 (PWR_CPU_ON)
unnamed: C29.2, U2.V14 (VDDA1V1_REG)
unnamed: R59.2, U14.L8 (ZQ)
unnamed: C67.2, U15.4 (BST)
unnamed: R61.1, R62.2, U15.6 (FB)
unnamed: C67.1, L1.1, U15.2 (SW)
unnamed: C68.2, U16.4 (BST)
unnamed: R63.1, R64.2, U16.6 (FB)
unnamed: C68.1, L2.1, U16.2 (SW)
unnamed: C69.2, U17.4 (BST)
unnamed: R65.1, R66.2, U17.6 (FB)
unnamed: C69.1, L3.1, U17.2 (SW)
unnamed: C72.1, U18.3 (Noise)
unnamed: C56.1, R60.2, U19.1 (EN)
unnamed: C75.1, U19.3 (Noise)
unnamed: C24.2, U21.4 (BST)
unnamed: R80.1, R81.2, U21.6 (FB)
unnamed: C24.1, L4.1, U21.2 (SW)
VDD: BOOT0_2.1, BOOT0_2.2, C1.1, C88.2, C176.1, C185.1, C190.1, C197.1, C201.1, C202.1, C205.1, C207.1, C208.1, C209.1, C215.1, J6.1, S3.1, U2.AA12 (PDR_ON), U2.C15 (VDDSD2), U2.E12 (VDD), U2.E17 (VDDSD1), U2.G9 (VDD), U2.G13 (VDD), U2.J7 (VDD), U2.J9 (VDD), U2.J13 (VDD), U2.K2 (VDD_PLL), U2.L2 (VBAT), U2.M5 (VDD), U2.N7 (VDD), U2.N9 (VDD), U2.N12 (VDD), U2.R5 (VDD), U2.R7 (VDD), U2.R9 (VDD), U2.R12 (VDD), U2.U7 (VDD), U2.V2 (VDD_ANA), U2.W11 (VDD), U2.Y18 (VDD_PLL2), U18.1 (EN), U19.4 (OUT), U20.1 (IN)
VDDA: C31.2, C84.2, U2.U8 (VDDA), U18.4 (OUT)
VDDA_1V8: C32.2, U2.W15 (VDDA1V8_REG), U20.3 (EN)
VDD_CORE: C89.2, C188.1, C189.1, C195.1, C196.1, C199.1, C200.1, C203.1, C213.1, L1.2, R61.2, U2.G11 (VDD_CORE), U2.J11 (VDD_CORE), U2.J15 (VDD_CORE), U2.L7 (VDD_CORE), U2.L9 (VDD_CORE), U2.L13 (VDD_CORE), U2.N10 (VDD_CORE), U2.N13 (VDD_CORE), U2.N15 (VDD_CORE), U2.R10 (VDD_CORE), U2.R13 (VDD_CORE), U2.U12 (VDD_CORE), U2.U14 (VDD_CORE)
VDD_CPU: C40.2, C174.1, C177.1, C183.1, C186.1, C187.1, C191.1, C194.1, L4.2, R80.2, U2.E7 (VDD_CPU), U2.E10 (VDD_CPU), U2.G5 (VDD_CPU), U2.G7 (VDD_CPU), U2.G10 (VDD_CPU), U2.K5 (VDD_CPU), U2.K7 (VDD_CPU)
VDD_DDR: C81.2, C83.2, C91.2, C92.1, C94.1, C98.1, C99.1, C102.1, C103.1, C106.1, C175.1, C182.1, C184.1, C192.1, C193.1, C198.1, C204.1, C206.1, C211.1, C212.1, L3.2, R65.2, R70.1, R78.1, U2.E15 (VDDQ_DDR), U2.G15 (VDDQ_DDR), U2.G17 (VDDQ_DDR), U2.K15 (VDDQ_DDR), U2.K17 (VDDQ_DDR), U2.M15 (VDDQ_DDR), U2.M17 (VDDQ_DDR), U2.R15 (VDDQ_DDR), U2.R17 (VDDQ_DDR), U2.U15 (VDDQ_DDR), U14.A1 (VDDQ), U14.A8 (VDDQ), U14.B2 (VDD), U14.C1 (VDDQ), U14.C9 (VDDQ), U14.D2 (VDDQ), U14.D9 (VDD), U14.E9 (VDDQ), U14.F1 (VDDQ), U14.G7 (VDD), U14.H2 (VDDQ), U14.H9 (VDDQ), U14.K2 (VDD), U14.K8 (VDD), U14.N1 (VDD), U14.N9 (VDD), U14.R1 (VDD), U14.R9 (VDD)
VDD_USB: C76.2, U2.W14 (VDD3V3_USBHS), U20.5 (OUT)
VREF+: C33.2, C44.1, J2.27, J2.28, J2.63, J2.64, U2.W7 (VREF+), U13.2 (VO)
VREF_DDR: C13.2, C42.1, C43.1, C109.2, R70.2, R71.1, R78.2, R79.1, U2.T18 (DDR_VREF), U14.H1 (VREFDQ), U14.M8 (VREFCA)

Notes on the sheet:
I2C1_SCL
ADC-3
DFU Boot requires MP1-DFU-USB bootloader installed
SDMMC_CMD
I2C3_SCL
ADC2-2
microSD
SDMMC_D0
ADC-14
I2C3_SDA
ADC-5
SAI1_SD_B
ADC-17
ADC-12
1.22V - 1.38V, 1.35V for 1GHz. Rank 2?3? Ratio for 1.35V: 1.45:1 (14.7k/10k =>= 1.344V)
SAI1_FS
ADC-8
SAI1_MCLK
ADC-6
POWER
SDMMC_D3
SD_CARD_DETECT
I2C5_SDA
ADC-2
SPI3_NSS
BOOT SWITCHES
ADC-13
SDMMC_CLK
Changes from v0.3/v0.4: DEBUG header pin 1 changed from GND to +3.3V
Befaco-mp13x
AN5586, Sec 5.3.1 The VDDCPU can always be set at 1.35 V allowing the CPU to work in Run mode (CPU frequency lower than 650 MHz) and in Run overdrive mode (CPU frequency higher than 650 MHz). This simplifies the VDDCPU VRM design to manage a single output voltage (1.35 V) and to free the PWR_OVRDRV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
SPI1-MOSI
SPI4_MOSI
SPI3-SCK
SAI1_SD_A
SPI3-MISO
SWD PROGRAMMING
SPI3_MOSI
Place these on pins:
3.3V for peripherals Rank 2
